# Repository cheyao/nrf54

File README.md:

# nRF54L15 devboard

This is a nRF54L15 devoard with a nRF52820 support mcu and a nPM1300 PMIC. The board supports logic I/O levels from 1.7V to 3.3V, adjustable in 100mV steps.

The top-board also allows battery input, allowing ultra low pwoered operation

Bottom board acts as a portable programmer, but can also be broken in half to act as a standalone bluetooth IC

Both schematics can act as standalone modules and be used sperately, they communicate only via a SDIO and UART bus.

The nrf54L15 is also equiped with an external 32.768kHz oscillator, in order to improve battery efficiency.

Cost:

- PCB: 27$
- Stencil: 7$
- Components $56
- Shipping: Depends on region

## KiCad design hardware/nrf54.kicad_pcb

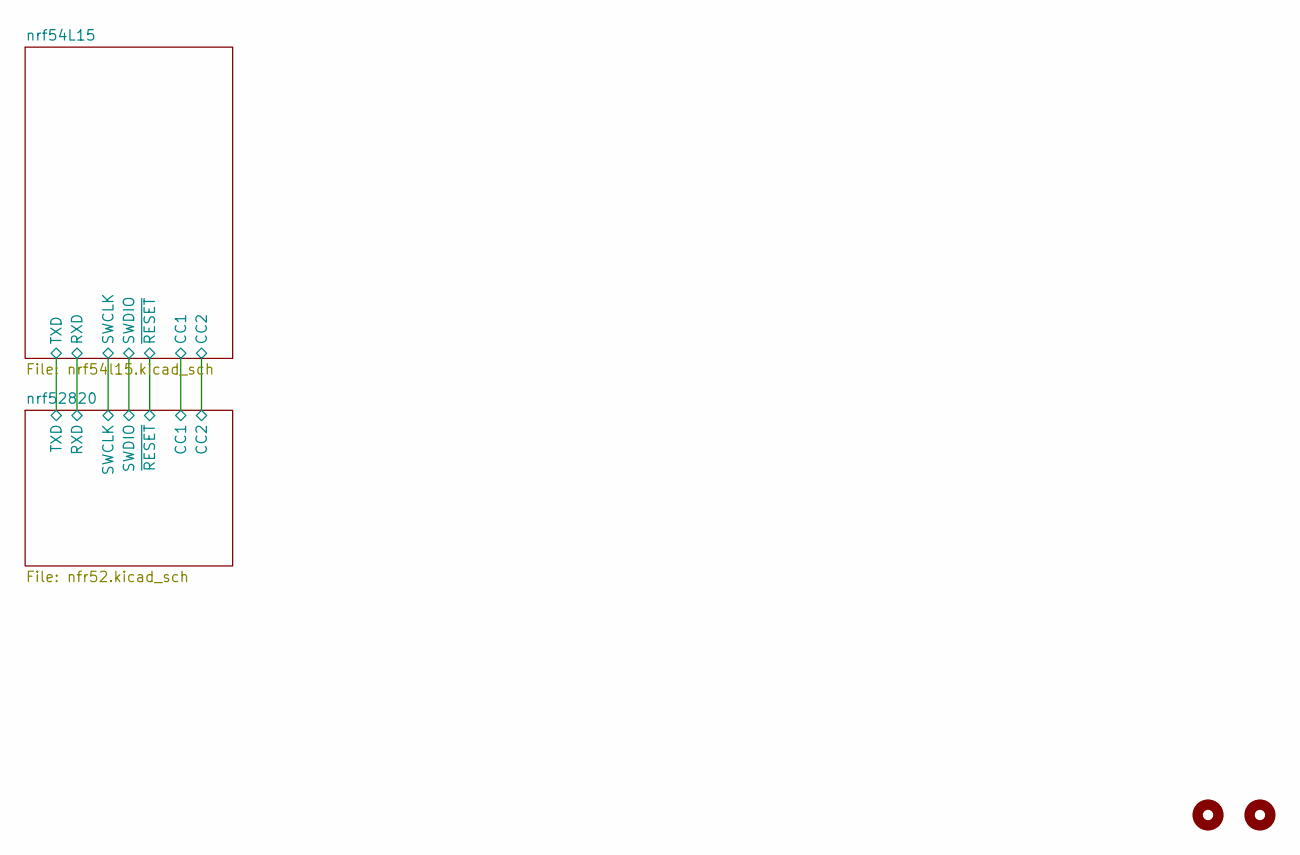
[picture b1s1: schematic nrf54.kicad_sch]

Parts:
H3, H4: MountingHole; MouseBite-Slot_2.0x2.0mm_outset_D0.5mm_P0.85mm_2h_Trace

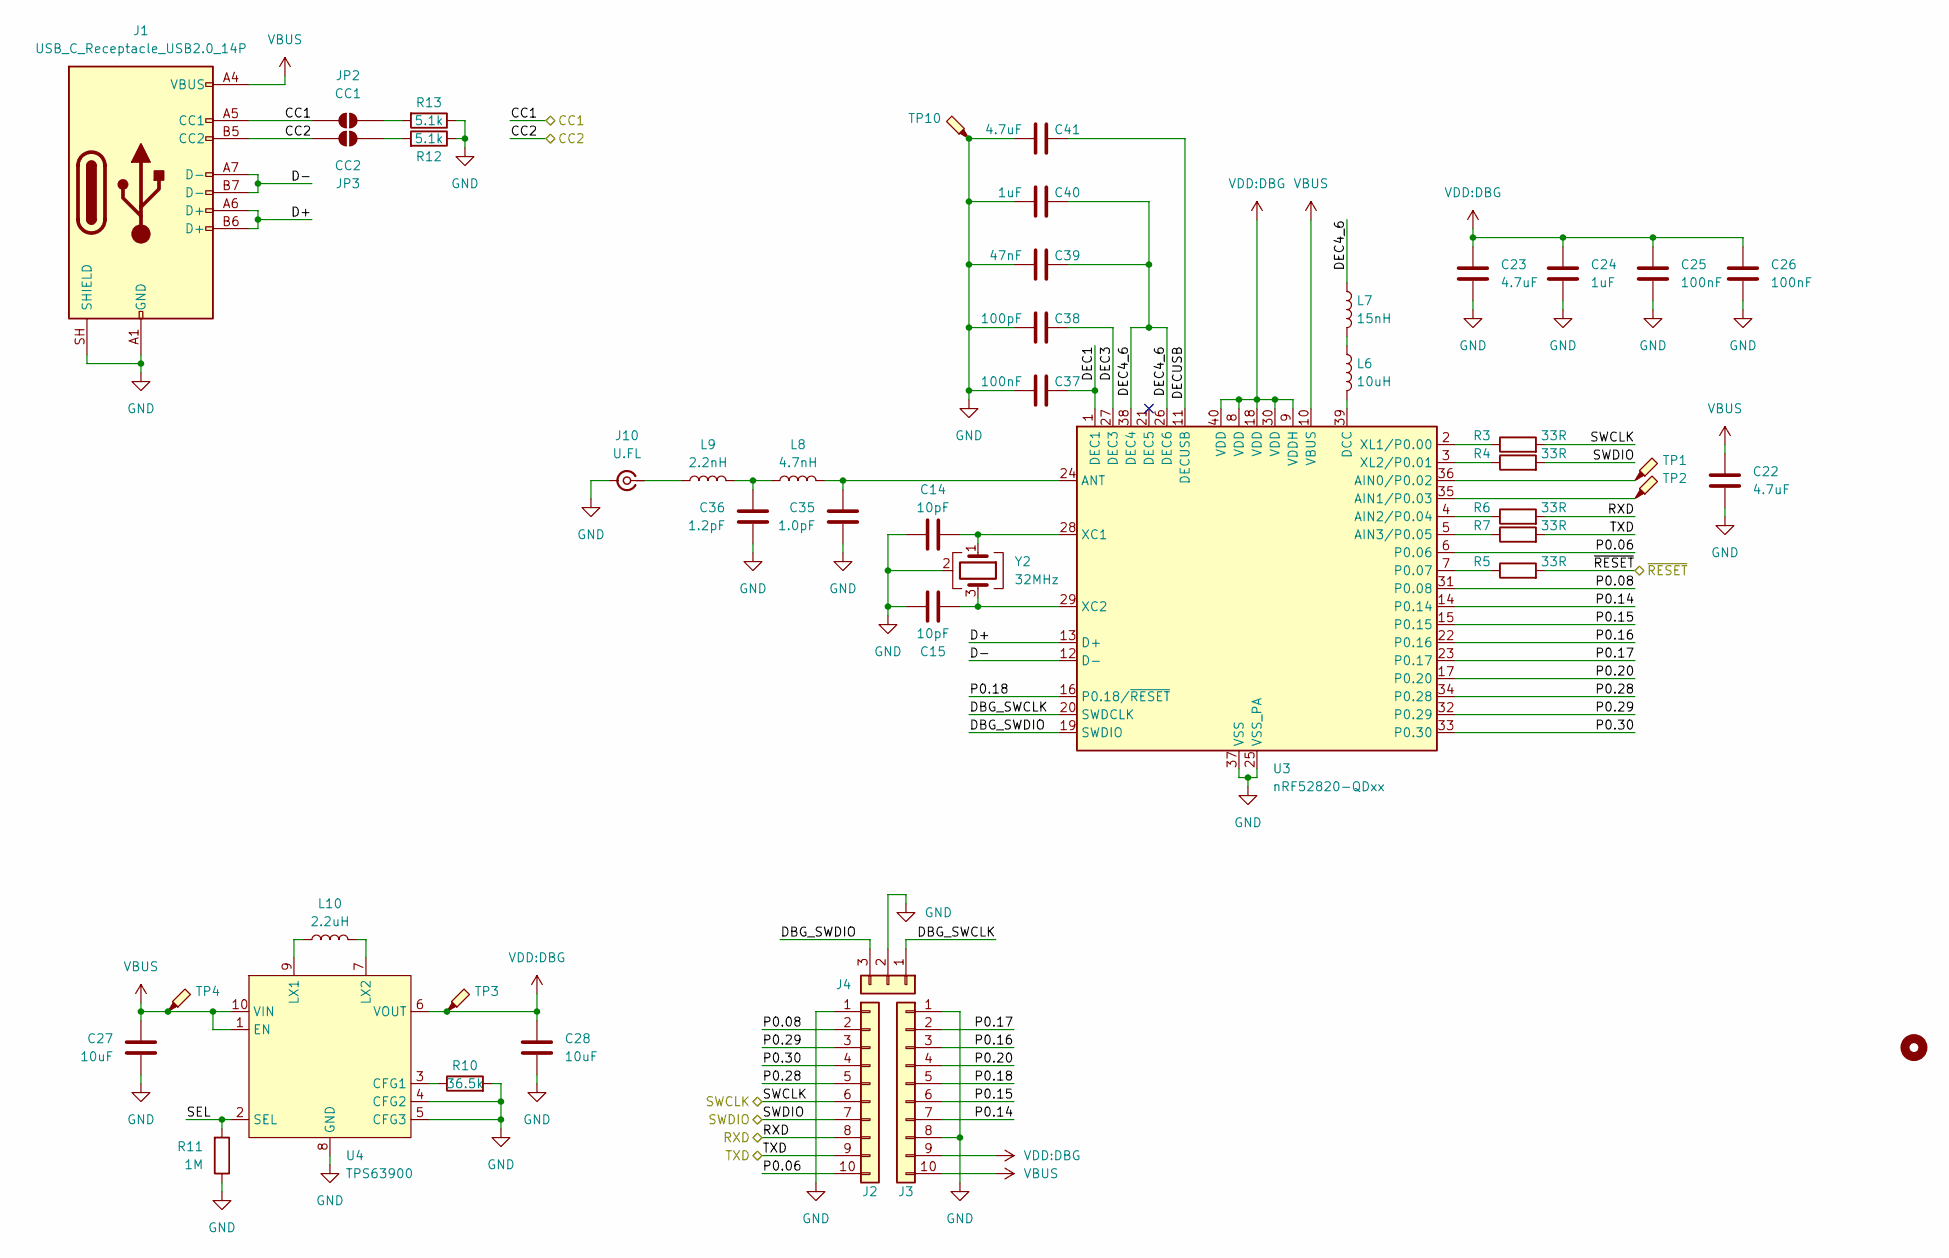
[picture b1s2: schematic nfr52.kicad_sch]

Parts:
C14, C15: 10pF; C_0402_1005Metric
C22, C23, C41: 4.7uF; C_0603_1608Metric
C24, C40: 1uF; C_0603_1608Metric
C25, C26, C37: 100nF; C_0402_1005Metric
C27, C28: 10uF; C_0603_1608Metric
C35: 1.0pF; C_0201_0603Metric
C36: 1.2pF; C_0201_0603Metric
C38: 100pF; C_0402_1005Metric
C39: 47nF; C_0402_1005Metric
H1: MountingHole; Icy Electronics Logo
J1: USB_C_Receptacle_USB2.0_14P; USB_C_Receptacle_HRO_TYPE-C-31-M-12
J2, J3: Conn_01x10; PinHeader_1x10_P2.54mm_Vertical
J4: Conn_01x03; PinHeader_1x03_P2.54mm_Vertical
J10: U.FL; U.FL_Hirose_U.FL-R-SMT-1_Vertical
JP2: CC1; SolderJumper-2_Open_Pad_Small
JP3: CC2; SolderJumper-2_Open_Pad_Small
L6: 10uH; L_0603_1608Metric
L7: 15nH; L_0402_1005Metric
L8: 4.7nH; L_0201_0603Metric
L9: 2.2nH; L_0201_0603Metric
L10: 2.2uH; L_1008_2520Metric; LCSC Part # C22471111
R3, R4, R5, R6, R7: 33R; R_0402_1005Metric
R10: 36.5k; R_0402_1005Metric
R11: 1M; R_0402_1005Metric
R12, R13: 5.1k; R_0402_1005Metric
TP1, TP2, TP3, TP4, TP10: TestPoint_Probe; TestPoint_Pad_D1.0mm
U3: nRF52820-QDxx; QFN-40-1EP_5x5mm_P0.4mm_EP3.6x3.6mm_ThermalVias
U4: TPS63900; WSON-10-1EP_2.5x2.5mm_P0.5mm_EP1.2x2mm_ThermalVias; LCSC Part # C1518762
Y2: 32MHz; Crystal_SMD_2016-4Pin_2.0x1.6mm; LCSC Part # C5339095

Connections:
/nrf52820/CC1: J1.A5 (CC1), JP2.1 (A); also elsewhere on the board
/nrf52820/CC2: J1.B5 (CC2), JP3.1 (A); also elsewhere on the board
/nrf52820/D+: J1.A6 (D+), J1.B6 (D+), U3.13 (D+)
/nrf52820/D-: J1.A7 (D-), J1.B7 (D-), U3.12 (D-)
/nrf52820/DBG_SWCLK: J4.1, U3.20 (SWDCLK)
/nrf52820/DBG_SWDIO: J4.3, U3.19 (SWDIO)
/nrf52820/DEC1: C37.2, U3.1 (DEC1)
/nrf52820/DEC3: C38.2, U3.27 (DEC3)
/nrf52820/DEC4_6: C39.2, C40.2, L7.1, U3.26 (DEC6), U3.38 (DEC4)
/nrf52820/DECUSB: C41.2, U3.11 (DECUSB)
/nrf52820/P0.06: J2.10, U3.6 (P0.06)
/nrf52820/P0.08: J2.2, U3.31 (P0.08)
/nrf52820/P0.14: J3.7, U3.14 (P0.14)
/nrf52820/P0.15: J3.6, U3.15 (P0.15)
/nrf52820/P0.16: J3.3, U3.22 (P0.16)
/nrf52820/P0.17: J3.2, U3.23 (P0.17)
/nrf52820/P0.18: J3.5, U3.16 (P0.18/~RESET)
/nrf52820/P0.20: J3.4, U3.17 (P0.20)
/nrf52820/P0.28: J2.5, U3.34 (P0.28)
/nrf52820/P0.29: J2.3, U3.32 (P0.29)
/nrf52820/P0.30: J2.4, U3.33 (P0.30)
/nrf52820/RXD: J2.8, R6.2; also elsewhere on the board
/nrf52820/SEL: R11.2, U4.2 (SEL)
/nrf52820/SWCLK: J2.6, R3.2; also elsewhere on the board
/nrf52820/SWDIO: J2.7, R4.2; also elsewhere on the board
/nrf52820/TXD: J2.9, R7.2; also elsewhere on the board
/nrf52820/~RESET: R5.2; also elsewhere on the board
GND: C14.1, C15.1, C22.2, C23.2, C24.2, C25.2, C26.2, C27.2, C28.2, C35.2, C36.2, C37.1, C38.1, C39.1, C40.1, C41.1, J1.A1 (GND), J1.A12 (GND), J1.B1 (GND), J1.B12 (GND), J1.SH (SHIELD), J2.1, J3.1, J3.8, J4.2, J10.2 (Ext), R10.2, R11.1, R12.1, R13.1, TP10.1 (1_1), U3.25 (VSS_PA), U3.37 (VSS), U3.41 (VSS), U4.4 (CFG2), U4.5 (CFG3), U4.8 (GND), U4.11 (GND), Y2.2 (G), Y2.4 (G); also elsewhere on the board
unnamed: C36.1, L8.1, L9.2
unnamed: J10.1 (In), L9.1
unnamed: JP2.2 (B), R13.2
unnamed: JP3.2 (B), R12.2
unnamed: L6.1, L7.2
unnamed: TP1.1 (1_1), U3.36 (AIN0/P0.02)
unnamed: TP2.1 (1_1), U3.35 (AIN1/P0.03)
unnamed: R6.1, U3.4 (AIN2/P0.04)
unnamed: R7.1, U3.5 (AIN3/P0.05)
unnamed: C35.1, L8.2, U3.24 (ANT)
unnamed: L6.2, U3.39 (DCC)
unnamed: R5.1, U3.7 (P0.07)
unnamed: C14.2, U3.28 (XC1), Y2.1
unnamed: C15.2, U3.29 (XC2), Y2.3
unnamed: R3.1, U3.2 (XL1/P0.00)
unnamed: R4.1, U3.3 (XL2/P0.01)
unnamed: R10.1, U4.3 (CFG1)
unnamed: L10.1, U4.9 (LX1)
unnamed: L10.2, U4.7 (LX2)
VBUS: C22.1, C27.1, J1.A4 (VBUS), J1.A9 (VBUS), J1.B4 (VBUS), J1.B9 (VBUS), J3.10, TP4.1 (1_1), U3.10 (VBUS), U4.1 (EN), U4.10 (VIN); also elsewhere on the board
VDD:DBG: C23.1, C24.1, C25.1, C26.1, C28.1, J3.9, TP3.1 (1_1), U3.8 (VDD), U3.9 (VDDH), U3.18 (VDD), U3.30 (VDD), U3.40 (VDD), U4.6 (VOUT)

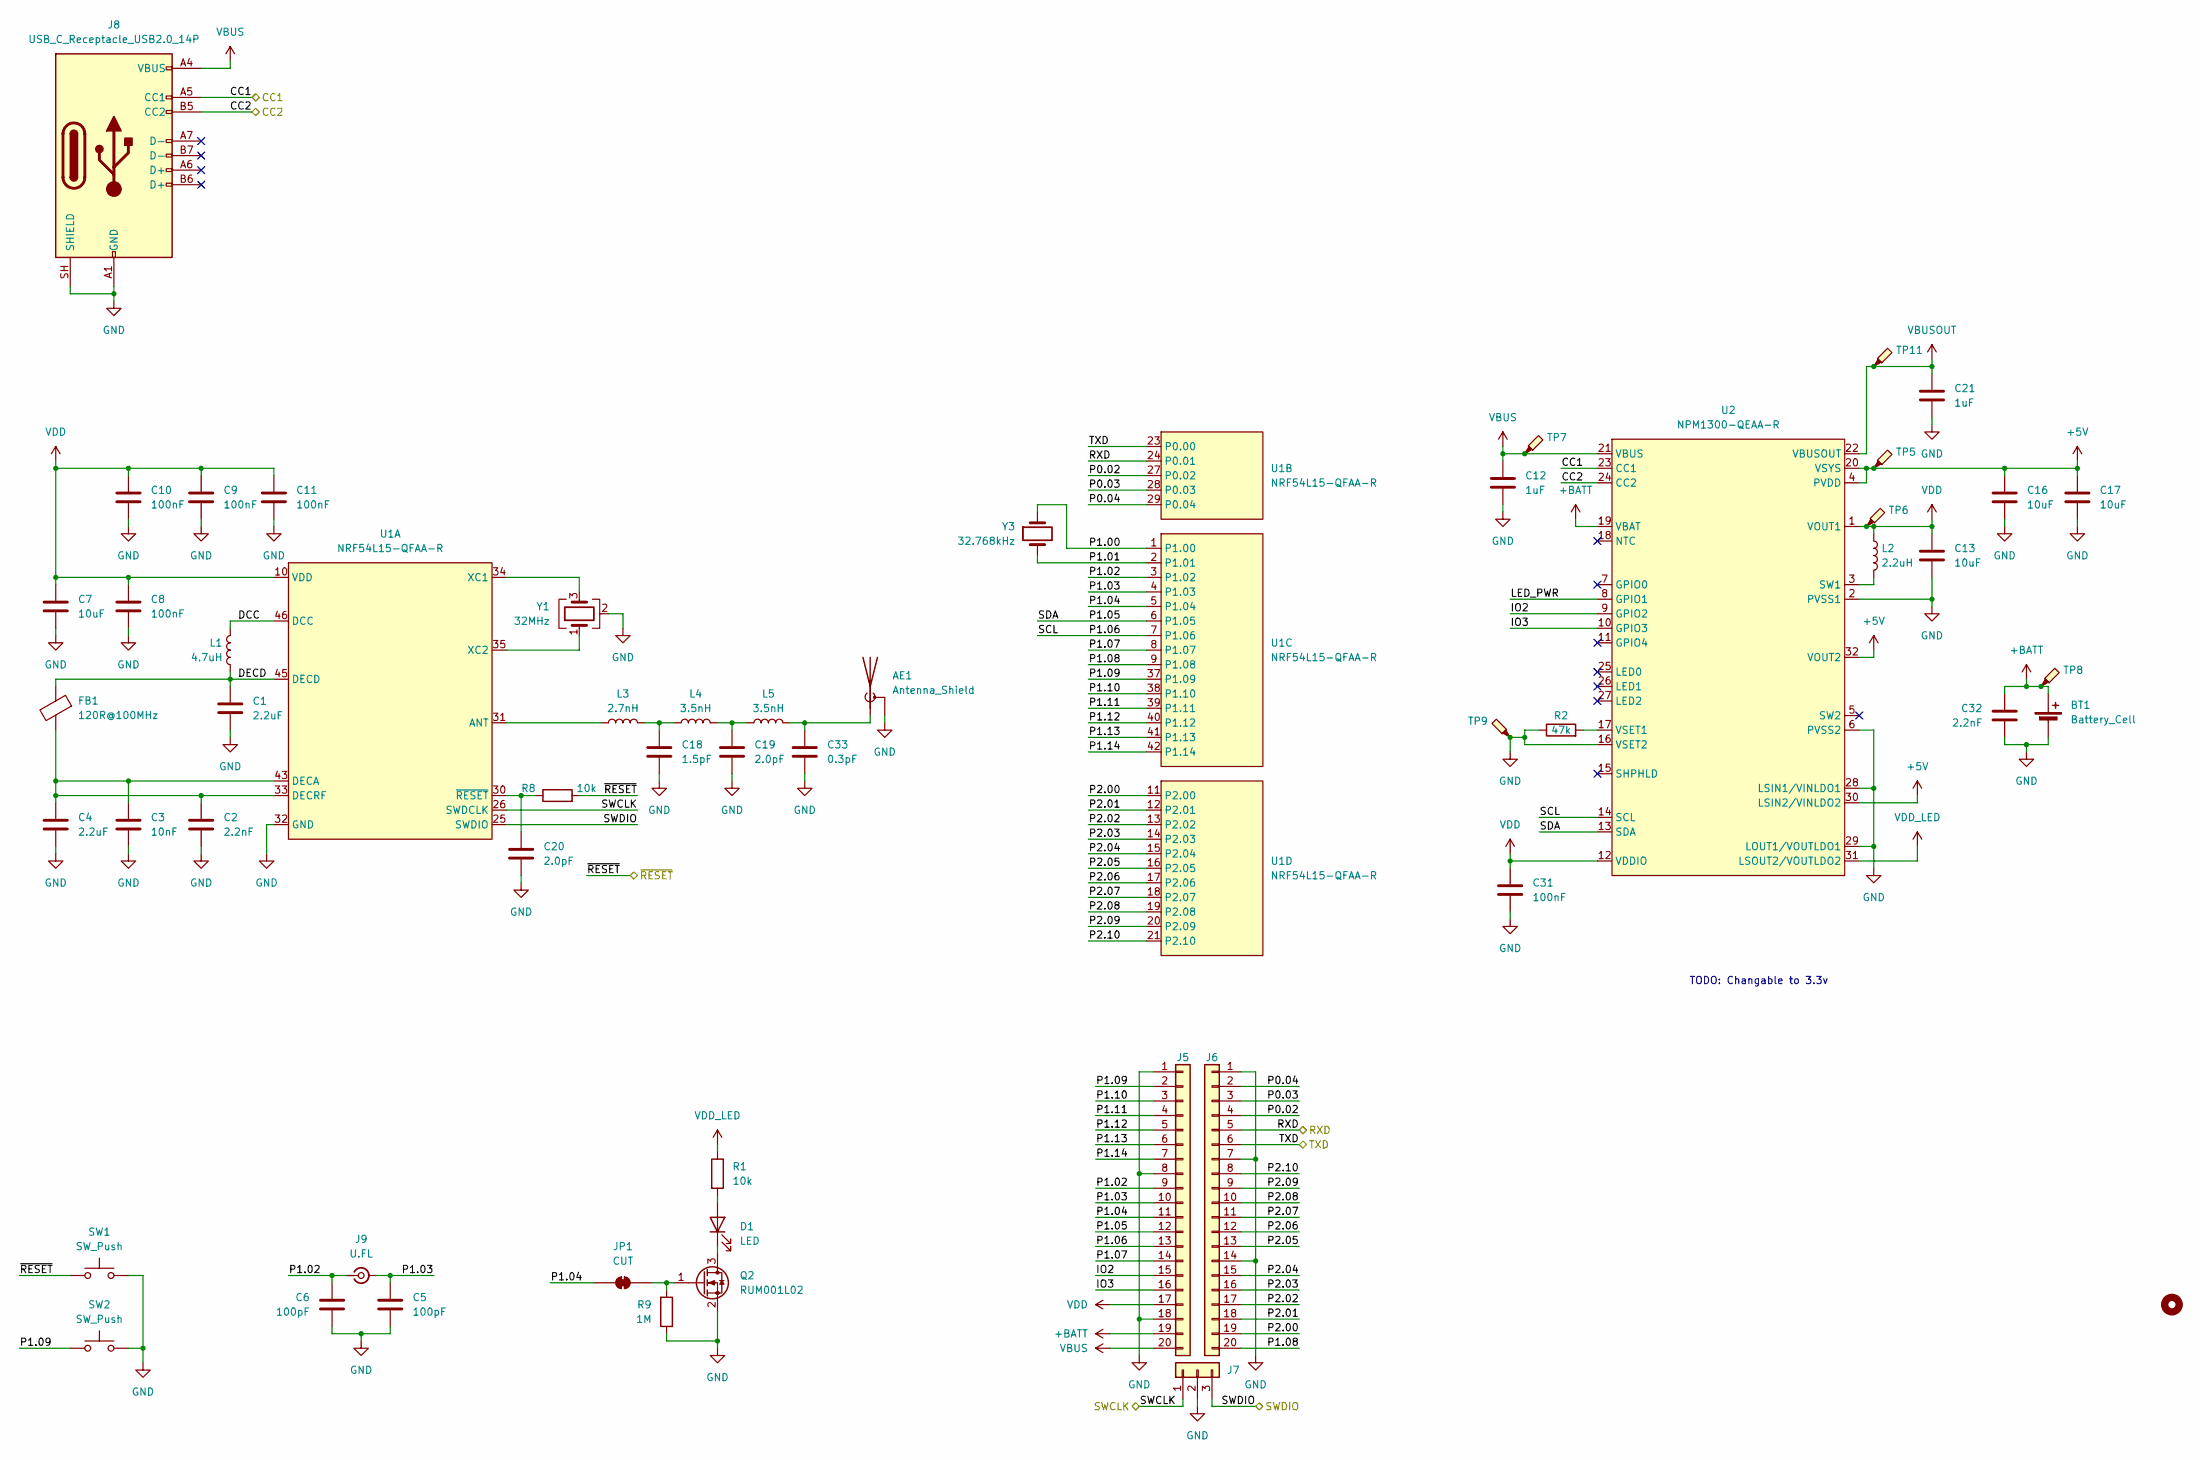
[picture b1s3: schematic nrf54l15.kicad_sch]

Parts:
AE1: Antenna_Shield; Texas_SWRA117D_2.4GHz_Right
BT1: Battery_Cell
C1, C4: 2.2uF; C_0402_1005Metric
C2, C32: 2.2nF; C_0402_1005Metric
C3: 10nF; C_0402_1005Metric
C5, C6: 100pF; C_0402_1005Metric
C7, C13, C16, C17: 10uF; C_0603_1608Metric
C8, C9, C10, C11, C31: 100nF; C_0402_1005Metric
C12, C21: 1uF; C_0603_1608Metric
C18: 1.5pF; C_0201_0603Metric
C19: 2.0pF; C_0201_0603Metric
C20: 2.0pF; C_0402_1005Metric
C33: 0.3pF; C_0201_0603Metric
D1: LED; LED_0402_1005Metric
FB1: 120R@100MHz; L_0402_1005Metric
H2: MountingHole; Icy Electronics Logo
J5, J6: Conn_01x20; PinHeader_1x20_P2.54mm_Vertical
J7: Conn_01x03; PinHeader_1x03_P2.54mm_Vertical
J8: USB_C_Receptacle_USB2.0_14P; USB_C_Receptacle_HRO_TYPE-C-31-M-12
J9: U.FL; U.FL_Hirose_U.FL-R-SMT-1_Vertical
JP1: CUT; SolderJumper-2_Bridged_Pad_Small
L1: 4.7uH; L_0603_1608Metric
L2: 2.2uH; L_1008_2520Metric; LCSC Part # C22471111
L3: 2.7nH; L_0201_0603Metric
L4, L5: 3.5nH; L_0201_0603Metric
Q2: RUM001L02; SOT-723; LCSC Part # C253528
R1, R8: 10k; R_0402_1005Metric
R2: 47k; C_0402_1005Metric
R9: 1M; R_0402_1005Metric
SW1, SW2: SW_Push; SW_Push_SPST_TSA016
TP5, TP6, TP7, TP8, TP9, TP11: TestPoint_Probe; TestPoint_Pad_D1.0mm
U1: NRF54L15-QFAA-R; QFN-48-1EP_6x6mm_P0.4mm_EP4.6x4.6mm_ThermalVias
U2: NPM1300-QEAA-R; VQFN-32-1EP_5x5mm_P0.5mm_EP3.5x3.5mm_ThermalVias
Y1: 32MHz; Crystal_SMD_2016-4Pin_2.0x1.6mm; LCSC Part # C5339095
Y3: 32.768kHz; Crystal_SMD_2012-2Pin_2.0x1.2mm; LCSC Part # C99009

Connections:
+5V: C16.1, C17.1, TP5.1 (1_1), U2.4 (PVDD), U2.20 (VSYS), U2.30 (LSIN2/VINLDO2), U2.32 (VOUT2)
+BATT: BT1.1 (+), C32.1, J5.19, TP8.1 (1_1), U2.19 (VBAT)
/nrf54L15/DCC: L1.2, U1.46 (DCC)
/nrf54L15/DECD: C1.1, FB1.1, L1.1, U1.45 (DECD)
/nrf54L15/IO2: J5.15, U2.9 (GPIO2)
/nrf54L15/IO3: J5.16, U2.10 (GPIO3)
/nrf54L15/LED_PWR: U2.8 (GPIO1)
/nrf54L15/P0.02: J6.4, U1.27 (P0.02)
/nrf54L15/P0.03: J6.3, U1.28 (P0.03)
/nrf54L15/P0.04: J6.2, U1.29 (P0.04)
/nrf54L15/P1.00: U1.1 (P1.00), Y3.1
/nrf54L15/P1.01: U1.2 (P1.01), Y3.2
/nrf54L15/P1.02: C6.1, J5.9, J9.1 (In), U1.3 (P1.02)
/nrf54L15/P1.03: C5.1, J5.10, J9.2 (Ext), U1.4 (P1.03)
/nrf54L15/P1.04: J5.11, JP1.1 (A), U1.5 (P1.04)
/nrf54L15/P1.05: J5.12, U1.6 (P1.05), U2.13 (SDA)
/nrf54L15/P1.06: J5.13, U1.7 (P1.06), U2.14 (SCL)
/nrf54L15/P1.07: J5.14, U1.8 (P1.07)
/nrf54L15/P1.08: J6.20, U1.9 (P1.08)
/nrf54L15/P1.09: J5.2, SW2.1, U1.37 (P1.09)
/nrf54L15/P1.10: J5.3, U1.38 (P1.10)
/nrf54L15/P1.11: J5.4, U1.39 (P1.11)
/nrf54L15/P1.12: J5.5, U1.40 (P1.12)
/nrf54L15/P1.13: J5.6, U1.41 (P1.13)
/nrf54L15/P1.14: J5.7, U1.42 (P1.14)
/nrf54L15/P2.00: J6.19, U1.11 (P2.00)
/nrf54L15/P2.01: J6.18, U1.12 (P2.01)
/nrf54L15/P2.02: J6.17, U1.13 (P2.02)
/nrf54L15/P2.03: J6.16, U1.14 (P2.03)
/nrf54L15/P2.04: J6.15, U1.15 (P2.04)
/nrf54L15/P2.05: J6.13, U1.16 (P2.05)
/nrf54L15/P2.06: J6.12, U1.17 (P2.06)
/nrf54L15/P2.07: J6.11, U1.18 (P2.07)
/nrf54L15/P2.08: J6.10, U1.19 (P2.08)
/nrf54L15/P2.09: J6.9, U1.20 (P2.09)
/nrf54L15/P2.10: J6.8, U1.21 (P2.10)
/nrf52820/CC1: J8.A5 (CC1), U2.23 (CC1); also elsewhere on the board
/nrf52820/CC2: J8.B5 (CC2), U2.24 (CC2); also elsewhere on the board
/nrf52820/RXD: J6.5, U1.24 (P0.01); also elsewhere on the board
/nrf52820/SWCLK: J7.1, U1.26 (SWDCLK); also elsewhere on the board
/nrf52820/SWDIO: J7.3, U1.25 (SWDIO); also elsewhere on the board
/nrf52820/TXD: J6.6, U1.23 (P0.00); also elsewhere on the board
/nrf52820/~RESET: R8.2, SW1.1; also elsewhere on the board
GND: AE1.2 (Shield), BT1.2 (-), C1.2, C2.2, C3.2, C4.2, C5.2, C6.2, C7.2, C8.2, C9.2, C10.2, C11.2, C12.2, C13.2, C16.2, C17.2, C18.2, C19.2, C20.2, C21.2, C31.2, C32.2, C33.2, J5.1, J5.8, J5.18, J6.1, J6.7, J6.14, J7.2, J8.A1 (GND), J8.A12 (GND), J8.B1 (GND), J8.B12 (GND), J8.SH (SHIELD), Q2.2 (S), R2.1, R9.1, SW1.2, SW2.2, TP9.1 (1_1), U1.32 (GND), U1.44 (GND), U1.49 (GND), U2.2 (PVSS1), U2.6 (PVSS2), U2.16 (VSET2), U2.28 (LSIN1/VINLDO1), U2.29 (LOUT1/VOUTLDO1), U2.33 (GND), Y1.2 (G), Y1.4 (G); also elsewhere on the board
unnamed: AE1.1 (A), C33.1, L5.2
unnamed: C18.1, L3.2, L4.1
unnamed: C19.1, L4.2, L5.1
unnamed: D1.2 (A), R1.2
unnamed: D1.1 (K), Q2.3 (D)
unnamed: JP1.2 (B), Q2.1 (G), R9.2
unnamed: L3.1, U1.31 (ANT)
unnamed: C2.1, C3.1, C4.1, FB1.2, U1.33 (DECRF), U1.43 (DECA)
unnamed: U1.34 (XC1), Y1.3
unnamed: U1.35 (XC2), Y1.1
unnamed: C20.1, R8.1, U1.30 (~RESET)
unnamed: L2.2, U2.3 (SW1)
unnamed: R2.2, U2.17 (VSET1)
VBUS: C12.1, J5.20, J8.A4 (VBUS), J8.A9 (VBUS), J8.B4 (VBUS), J8.B9 (VBUS), TP7.1 (1_1), U2.21 (VBUS); also elsewhere on the board
VBUSOUT: C21.1, TP11.1 (1_1), U2.22 (VBUSOUT)
VDD: C7.1, C8.1, C9.1, C10.1, C11.1, C13.1, C31.1, J5.17, L2.1, TP6.1 (1_1), U1.10 (VDD), U1.22 (VDD), U1.36 (VDD), U1.47 (VDD), U1.48 (VDD), U2.1 (VOUT1), U2.12 (VDDIO)
VDD_LED: R1.1, U2.31 (LSOUT2/VOUTLDO2)

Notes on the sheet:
TODO: Changable to 3.3v

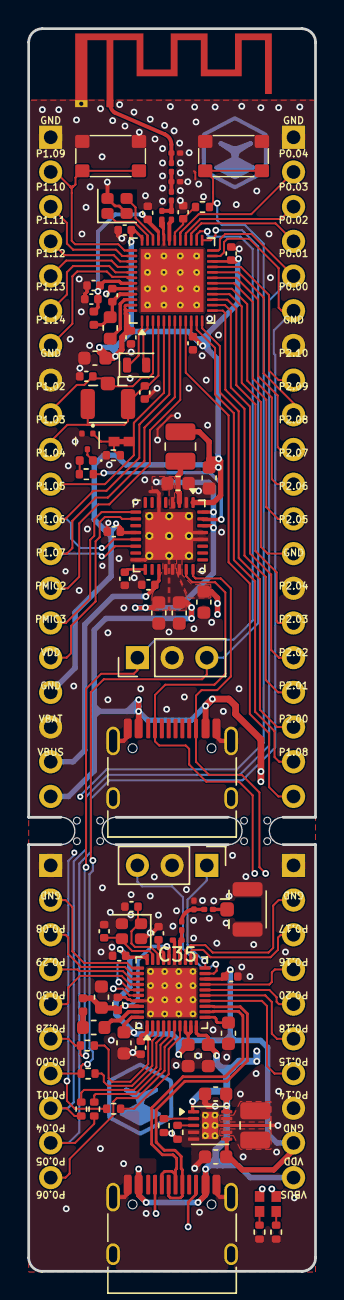
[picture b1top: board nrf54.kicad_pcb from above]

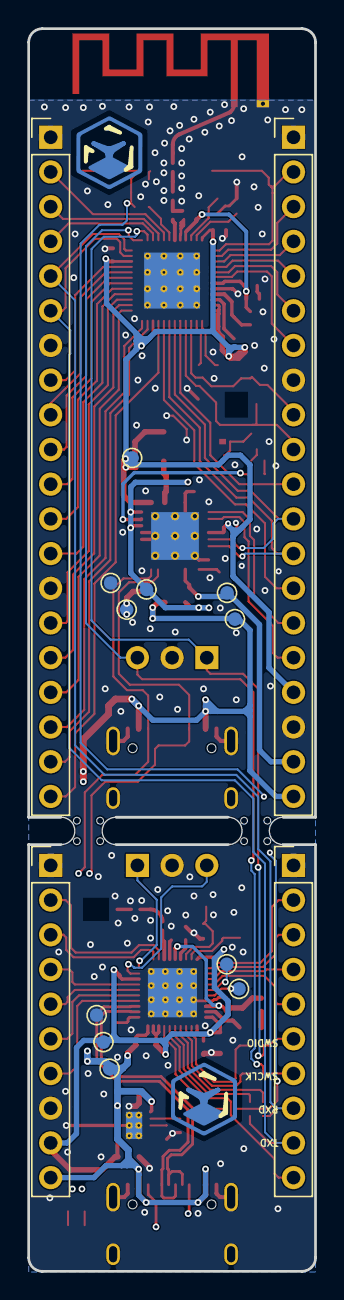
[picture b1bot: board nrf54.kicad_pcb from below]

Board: 4 copper layers, 21.0 x 91.0 mm, 102 parts (17 on the bottom side), 100 nets.

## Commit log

2026-06-11 Init
